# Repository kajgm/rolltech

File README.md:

# Rolltech - Chairable

Roll Technology presents Chairable, a revolutionary product designed to explore the immature field of spherical wheel technology.

- Chairable utilizes a spherical wheel design for tight maneuvering and a space-efficient footprint
- Leverages an adjustable clamping mechanisim to enable modular attachment to a variety of office chairs
- A large 7000mAh lithium polymer battery and a powerful 2200W motor provide the ability to move a 125kg load at a 2.5m/s pace
- Uses a carefully crafted mechanical design implemented with machined steel and custom 3D printed elements
- A safe and robust experience is achieved through a fully enclosed electrical circuit with 14+ motor control, logic, and safety elements
- Operated remotely using a tailored PCB design, a custom controller casing, and a specifically crafted low-power circuit.

## About

Roll Technology is a [Simon Fraser University based Capstone Project](https://summit.sfu.ca/person/81237) group comprised of five 5th year engineering students.

## Folder structure

- PCB - Custom pcb design documents including KiCad schematics
- docs - Design related documentation, company branding, and user manual
- solidworks - Solidworks .STL and .SLDPRT files as well as drawn diagrams
- src - Arduino code relating to the controller device communication and logic

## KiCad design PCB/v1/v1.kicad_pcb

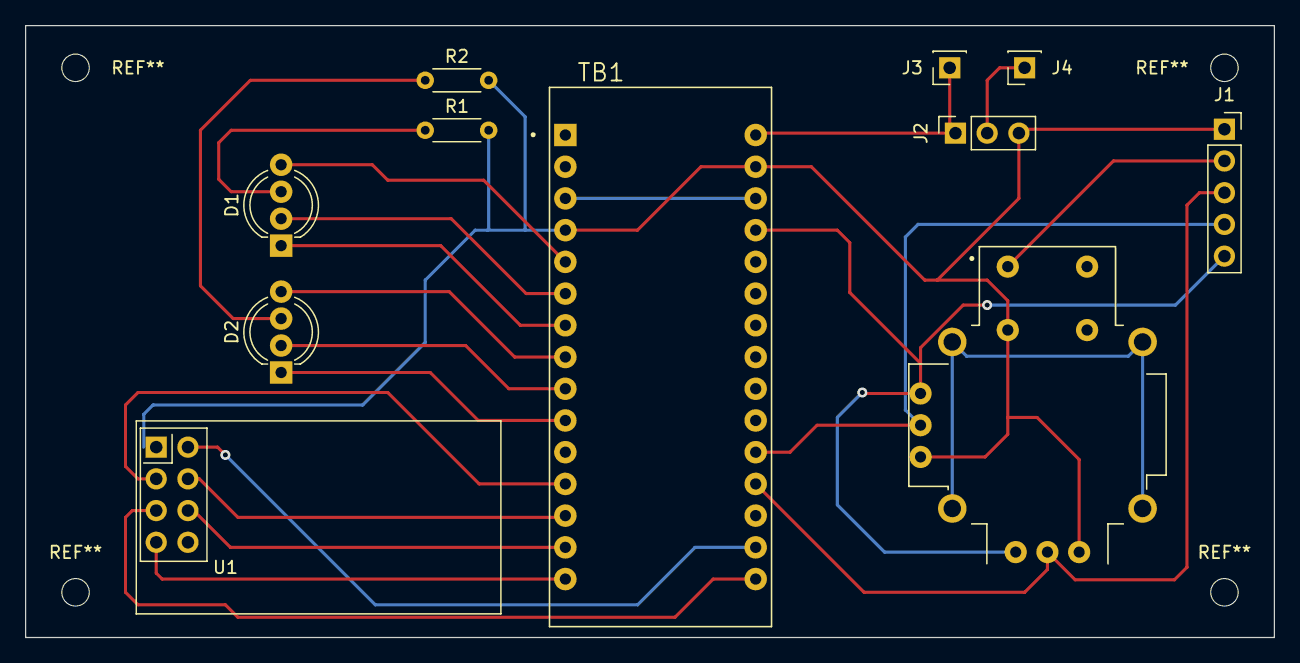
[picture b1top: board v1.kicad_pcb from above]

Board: 2 copper layers, 100.0 x 49.0 mm, 11 parts (0 on the bottom side), 21 nets.

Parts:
D1, D2: LED_BGAR; LED_D5.0mm-4_RGB_Wide_Pins
J1: Conn_01x05; PinSocket_1x05_P2.54mm_Vertical
J2: Conn_01x03; PinSocket_1x03_P2.54mm_Vertical
J3, J4: Conn_01x01; PinSocket_1x01_P2.54mm_Vertical
R1, R2: R; R_Axial_DIN0204_L3.6mm_D1.6mm_P5.08mm_Horizontal
TB1: ARDUINO_NANO; SHIELD_ARDUINO_NANO
U1: NRF24L01_Breakout; nRF24L01_Breakout
U2: COM-09032; XDCR_COM-09032

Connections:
GND: J1.1, J2.3, R1.2, R2.2, TB1.4 (COM/GND), TB1.29 (COM/GND), U1.1 (GND), U2.B2A (SEL-), U2.H3 (H-), U2.V3 (V-)
unnamed: D1.3 (A), R1.1
unnamed: D1.1 (BK), TB1.7 (D4)
unnamed: D1.2 (GK), TB1.6 (D3)
unnamed: D1.4 (RK), TB1.5 (D2)
unnamed: D2.3 (A), R2.1
unnamed: D2.1 (BK), TB1.10 (D7)
unnamed: D2.2 (GK), TB1.9 (D6)
unnamed: D2.4 (RK), TB1.8 (D5)
unnamed: J1.2, U2.B1A (SEL+)
unnamed: J1.3, TB1.19 (A0), U2.H2 (H)
unnamed: J1.4, TB1.20 (A1), U2.V2 (V)
unnamed: J1.5, TB1.27 (+5V), U2.H1 (H+), U2.V1 (V+)
unnamed: J2.1, J3.1, TB1.30 (VIN)
unnamed: J2.2, J4.1
unnamed: TB1.17 (3V3), U1.2 (VCC)
unnamed: TB1.12 (D9), U1.3 (CE)
unnamed: TB1.13 (D10), U1.4 (~CSN)
unnamed: TB1.14 (D11/MOSI), U1.6 (MOSI)
unnamed: TB1.15 (D12/MISO), U1.7 (MISO)
unnamed: TB1.16 (D13/SCK), U1.5 (SCK)

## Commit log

2023-06-22 feat: initial arduino sketch
2023-06-22 added readme.md
2023-06-25 added dual motor functionality with joystick
2023-06-26 update values
2023-06-26 Init Commit
2023-06-26 Refactored entire code into embedded files
2023-07-02 poc circuit for demo day
2023-07-02 refactor to main
2023-07-02 cleanup of logic and added comments
2023-07-02 minor fix
2023-07-02 fix logic issues
2023-07-02 minor variable change
2023-07-17 added rf module code
2023-07-18 added LED signalling
2023-07-25 added support for main driver motor
2023-07-28 added rf testing
2023-07-30 added speed limit
2023-08-17 docs: added info to readme.md
2023-08-17 fixed minor image typo
2023-08-17 minor readme.md layout improvements
2023-09-06 added final 405 docs
2023-09-10 next iteration of part schematics
2023-09-15 updated schematics
2023-09-15 removed speed limiter
2023-09-18 revert speed adjustments and doc updates
2023-09-26 new schematics
2023-09-29 ring bracket schematics
2023-09-29 fixes to ring schematic
2023-10-02 Create controller
    PCB files for controller
2023-10-02 Add files via upload
    All the pcb files
2023-10-02 file structure refactor
2023-10-02 Added all of the solidworks files
2023-10-02 refactor of file structure
2023-10-08 updated schematics with final design
2023-10-13 updated sender and receiver
2023-10-24 updated models and circuit diagram
2023-11-04 user manual diagrams
2023-11-05 Correct input recognition
2023-11-06 minor fixes
2023-11-12 beta working version of software - TEST PASSED!
2023-11-12 init 3d model for controller casing
2023-11-12 Amend: init controller casing 3d model
2023-11-14 Added v2 of controller casing body
2023-11-14 Added rounded corners for casing bracket
2023-11-14 Added STL v3 controller casing with rounded edges
2023-11-19 fixed up rotation issue
2023-11-19 Added more versions of the controller casing
2023-11-20 3D Modelled More Casing Part
2023-11-20 3D Models of More Controller casing
2023-11-20 [SOFTWARE] Minor improvements to jitter due to input
2023-11-21 Basic accel implemented
2023-11-23 Final working code
2023-11-24 improved case
2023-11-24 Minor update on controller body and rename
2023-11-26 Final Working version of controller and driver
2023-11-26 Increased final speed to 15
2023-11-27 updates to controller casing and user manual pictures
2023-11-27 Flipped the joystick
2023-11-27 Reversed Flip and just switch FLeft and FRight
2023-11-29 Final code flips
2023-12-02 misc clean up of docs
2024-01-22 minor rewording
2024-06-03 add link to video
